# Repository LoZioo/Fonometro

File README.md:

# Fonometro
Progetto per IoT based smart systems sull'analisi acustica.

## Hardware circuit layout

## Final result

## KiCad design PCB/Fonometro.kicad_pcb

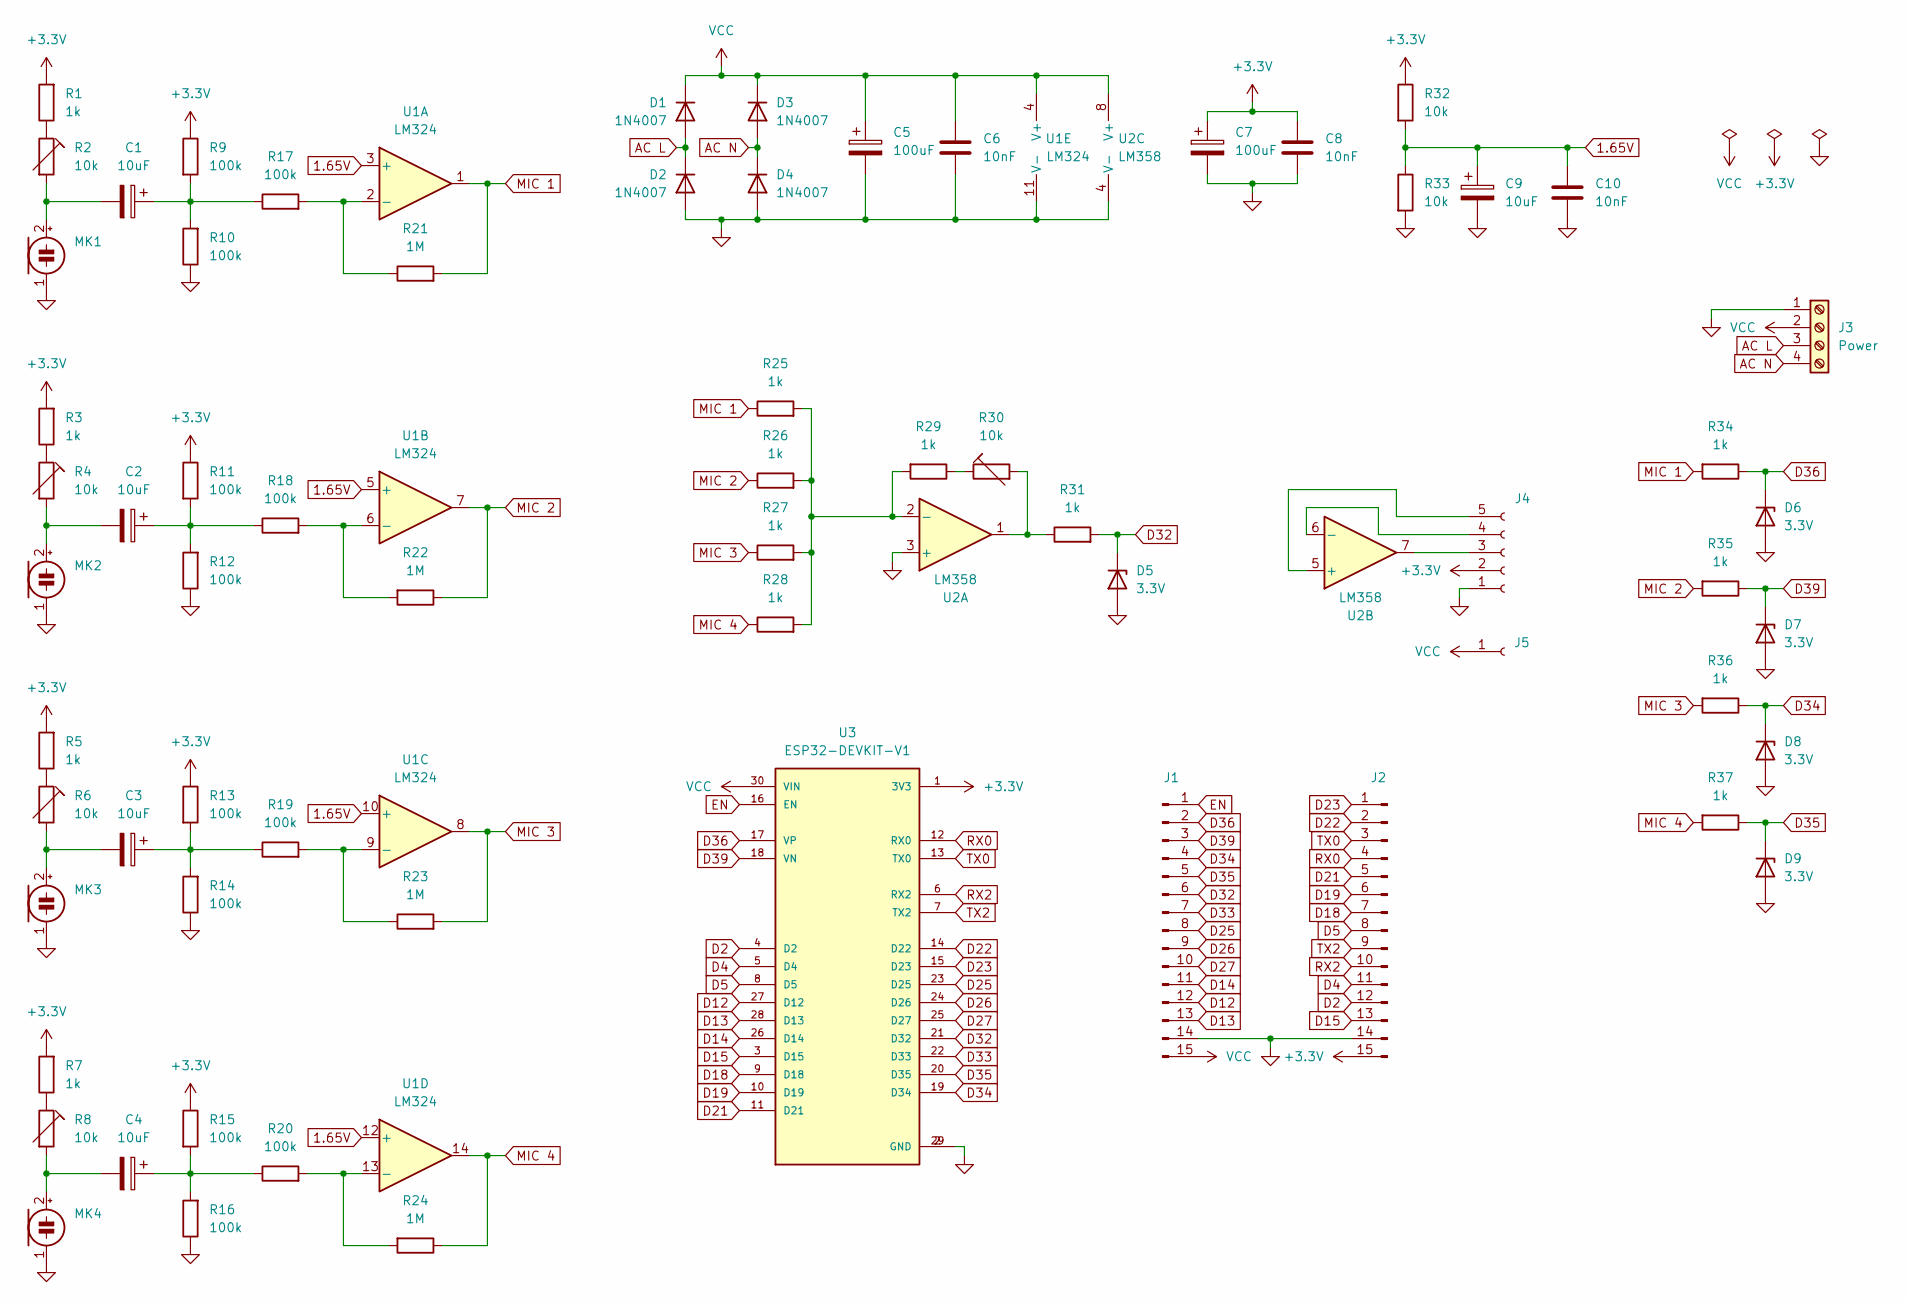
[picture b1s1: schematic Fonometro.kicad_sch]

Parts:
C1, C2, C3, C4, C9: 10uF; CP_Radial_D4.0mm_P1.50mm
C5, C7: 100uF; CP_Radial_D6.3mm_P2.50mm
C6, C8, C10: 10nF; C_Rect_L7.0mm_W2.5mm_P5.00mm
D1, D2, D3, D4: 1N4007; D_DO-41_SOD81_P7.62mm_Horizontal
D5, D6, D7, D8, D9: 3.3V; D_DO-41_SOD81_P7.62mm_Horizontal
J1, J2: Conn_01x15_Male; PinHeader_1x15_P2.54mm_Vertical
J3: Power; TerminalBlock_4Ucon_1x04_P3.50mm_Horizontal
J4: Conn_01x05_Female; PinHeader_1x05_P2.54mm_Vertical
J5: Conn_01x01_Female; PinHeader_1x01_P2.54mm_Vertical
MK1, MK2, MK3, MK4: Microphone_Condenser; PinHeader_1x02_P2.54mm_Vertical
R1, R3, R5, R7, R25, R26, R27, R28, R29, R31, R34, R35, R36, R37: 1k; R_Axial_DIN0207_L6.3mm_D2.5mm_P7.62mm_Horizontal
R2, R4, R6, R8, R30: 10k; Potentiometer_Runtron_RM-065_Vertical
R9, R10, R11, R12, R13, R14, R15, R16, R17, R18, R19, R20: 100k; R_Axial_DIN0207_L6.3mm_D2.5mm_P7.62mm_Horizontal
R21, R22, R23, R24: 1M; R_Axial_DIN0207_L6.3mm_D2.5mm_P7.62mm_Horizontal
R32, R33: 10k; R_Axial_DIN0207_L6.3mm_D2.5mm_P7.62mm_Horizontal
U1: LM324; DIP-14_W7.62mm_Socket
U2: LM358; DIP-8_W7.62mm_Socket
U3: ESP32-DEVKIT-V1; MODULE_ESP32_DEVKIT_V1; PARTREV N/A

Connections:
1.65V: C9.1, C10.1, R32.2, R33.1, U1.3 (+), U1.5 (+), U1.10 (+), U1.12 (+)
+3V3: C7.1, C8.1, J2.15, J4.2, R1.2, R3.2, R5.2, R7.2, R9.1, R11.1, R13.1, R15.1, R32.1, U3.1 (3V3)
AC L: D1.2 (A), D2.1 (K), J3.3
AC N: D3.2 (A), D4.1 (K), J3.4
D2: J2.12, U3.4 (D2)
D4: J2.11, U3.5 (D4)
D5: J2.8, U3.8 (D5)
D12: J1.12, U3.27 (D12)
D13: J1.13, U3.28 (D13)
D14: J1.11, U3.26 (D14)
D15: J2.13, U3.3 (D15)
D18: J2.7, U3.9 (D18)
D19: J2.6, U3.10 (D19)
D21: J2.5, U3.11 (D21)
D22: J2.2, U3.14 (D22)
D23: J2.1, U3.15 (D23)
D25: J1.8, U3.23 (D25)
D26: J1.9, U3.24 (D26)
D27: J1.10, U3.25 (D27)
D32: D5.1 (K), J1.6, R31.2, U3.21 (D32)
D33: J1.7, U3.22 (D33)
D34: D8.1 (K), J1.4, R36.1, U3.19 (D34)
D35: D9.1 (K), J1.5, R37.1, U3.20 (D35)
D36: D6.1 (K), J1.2, R34.1, U3.17 (VP)
D39: D7.1 (K), J1.3, R35.1, U3.18 (VN)
EN: J1.1, U3.16 (EN)
GND: C5.2, C6.2, C7.2, C8.2, C9.2, C10.2, D2.2 (A), D4.2 (A), D5.2 (A), D6.2 (A), D7.2 (A), D8.2 (A), D9.2 (A), J1.14, J2.14, J3.1, J4.1, MK1.1 (-), MK2.1 (-), MK3.1 (-), MK4.1 (-), R10.1, R12.1, R14.1, R16.1, R33.2, U1.11 (V-), U2.3 (+), U2.4 (V-), U3.2 (GND), U3.29 (GND)
MIC 1: R21.2, R25.1, R34.2, U1.1
MIC 2: R22.1, R26.1, R35.2, U1.7
MIC 3: R23.2, R27.1, R36.2, U1.8
MIC 4: R24.1, R28.1, R37.2, U1.14
unnamed: C1.1, R9.2, R10.2, R17.1
unnamed: C1.2, MK1.2 (+), R2.2
unnamed: C2.1, R11.2, R12.2, R18.1
unnamed: C2.2, MK2.2 (+), R4.2
unnamed: C3.1, R13.2, R14.2, R19.1
unnamed: C3.2, MK3.2 (+), R6.2
unnamed: C4.1, R15.2, R16.2, R20.1
unnamed: C4.2, MK4.2 (+), R8.2
unnamed: J4.3, U2.7
unnamed: J4.5, U2.5 (+)
unnamed: R1.1, R2.1
unnamed: R3.1, R4.1
unnamed: R5.1, R6.1
unnamed: R7.1, R8.1
unnamed: R17.2, R21.1, U1.2 (-)
unnamed: R18.2, R22.2, U1.6 (-)
unnamed: R19.2, R23.1, U1.9 (-)
unnamed: R20.2, R24.2, U1.13 (-)
unnamed: R25.2, R26.2, R27.2, R28.2, R29.2, U2.2 (-)
unnamed: R29.1, R30.1
unnamed: R30.2, R31.1, U2.1
unnamed: J4.4, U2.6 (-)
RX0: J2.4, U3.12 (RX0)
RX2: J2.10, U3.6 (RX2)
TX0: J2.3, U3.13 (TX0)
TX2: J2.9, U3.7 (TX2)
VCC: C5.1, C6.1, D1.1 (K), D3.1 (K), J1.15, J3.2, J5.1, U1.4 (V+), U2.8 (V+), U3.30 (VIN)

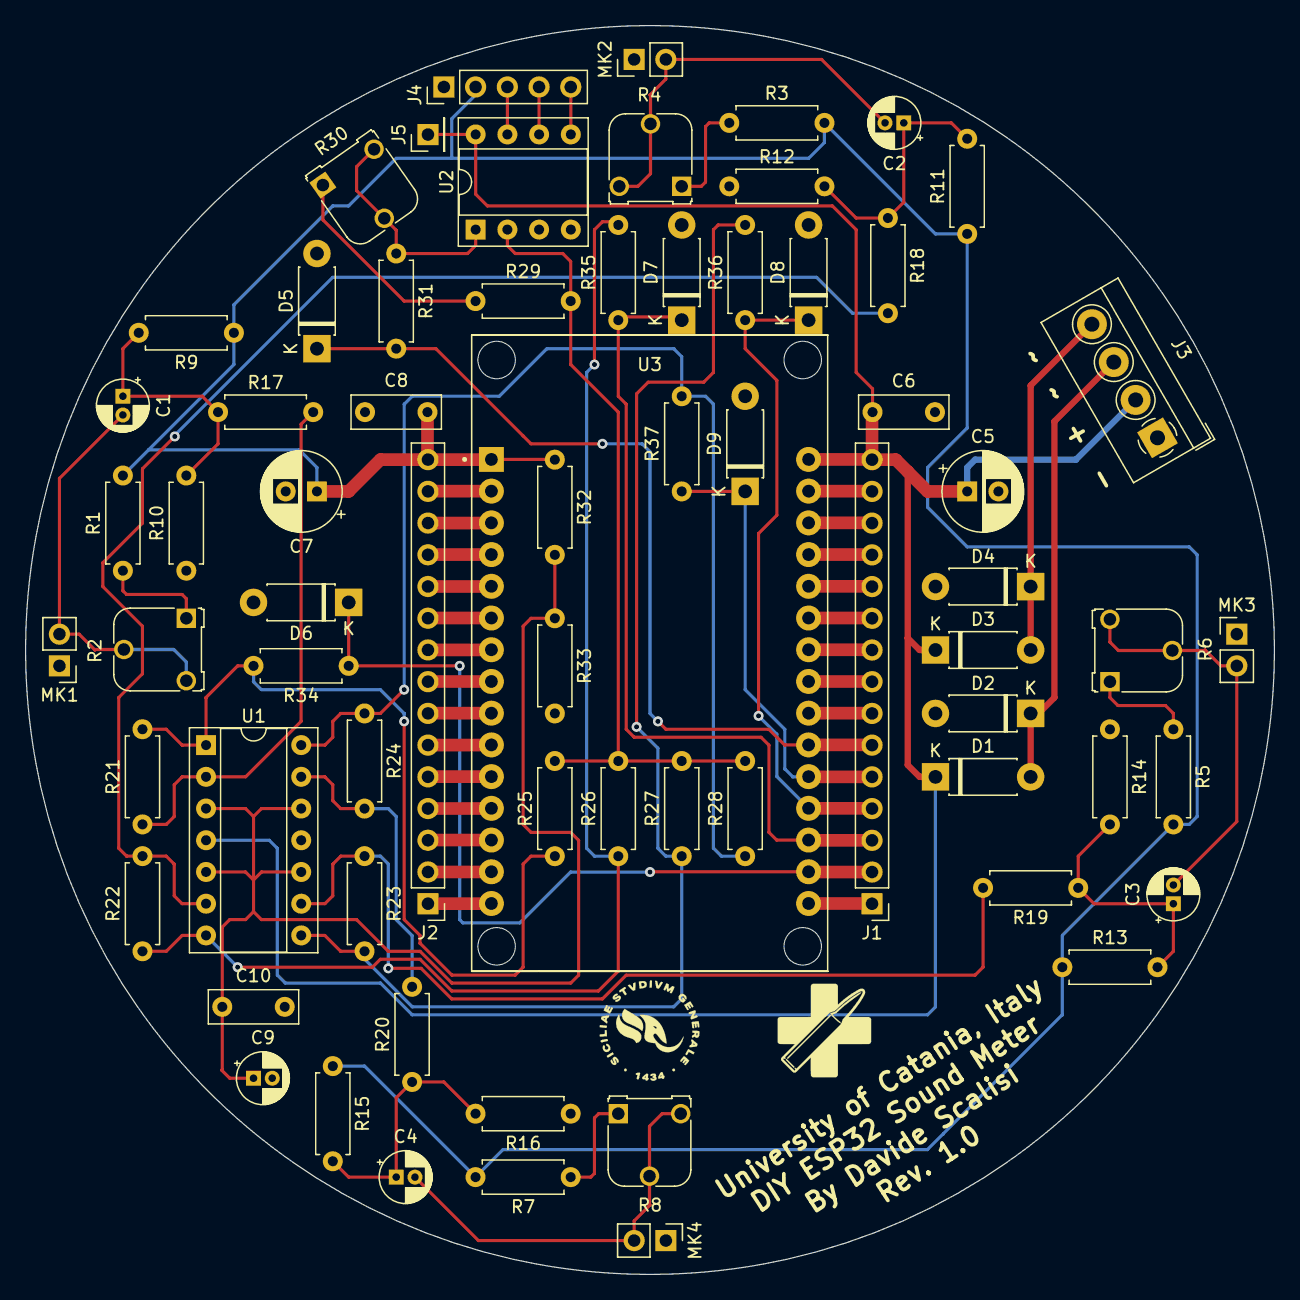
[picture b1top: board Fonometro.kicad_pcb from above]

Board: 2 copper layers, 100.0 x 100.0 mm, 68 parts (0 on the bottom side), 58 nets.

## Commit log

2023-02-02 feat: added first release of the circuit.
2023-02-03 feat: added .gitignore for KiCad files.
2023-02-03 feat: added power part and first PCB release.
2023-02-03 feat: improved PCB layout.
2023-02-04 feat: added single channel ADC input on MCU.
2023-02-04 feat: first working PCB release.
2023-02-05 feat: added Gerber.
2023-02-05 feat: J4 and J5 for U2B.
2023-02-05 fix: now U2A.+ is connected to 1.65V.
2023-02-05 feat: updated Gerbers.
2023-02-05 chore: removed Gerber zip from git.
2023-02-05 feat: project boilerplate.
2023-02-05 fix(upload_speed): now is 2.000.000 baud.
2023-02-05 chore: added password.h.
2023-02-05 chore(upload_speed): now is 115200.
2023-02-05 feat: threads test.
2023-02-05 feat: added samples generator script.
2023-02-05 feat: some DAC code.
2023-02-06 feat: added DAC sinewave generator.
2023-02-06 feat: added MIC GPIOs.
2023-02-06 feat: timer0 for sampling and timer1 for wavegen.
2023-02-06 refactor
2023-02-06 fix(IPC)
2023-02-06 fix(SAMPLING_FREQ)
2023-02-06 chore
2023-02-18 tidy
2023-02-19 chore: removed spaces.
2023-02-19 feat: removed manual sampling parameters.
2023-02-19 feat: wipe code; preparing for I2S implementation.
2023-02-19 fix(assert)
2023-02-19 feat
2023-02-19 feat(i2s base code)
2023-02-19 feat: added i2s sampling.
2023-02-19 feat: added some code.
2023-02-20 feat: added other test code.
2023-02-22 fix: now the db SPL conversion is working.
2023-02-22 feat: optimized memory usage.
2023-02-22 feat: implemented Knuth running mean algorithm.
2023-02-22 feat: begin FFT implementation.
2023-02-23 feat: fix and hrdly optimized memory usage.
2023-02-23 feat: added new FFT library.
2023-02-26 feat: beginning class translation.
2023-02-26 feat: first class release.
2023-02-26 feat: private empty constructor.
2023-02-26 chore: disabled SPL array calculation.
2023-02-26 feat: first working conversion to class.
2023-02-28 feat: from 32 bit sample to 16 bit sample.
2023-02-28 feat: captive portal dev. in progress...
2023-02-28 feat: added settings.bin.
2023-02-28 feat: added web libraries.
2023-02-28 feat: captive portal.
2023-03-01 feat: MQTT.
2023-10-05 docs: device's pictures.
